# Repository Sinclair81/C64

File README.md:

# C64 #

## TinyAdapter (for Tiny-EPROMer from FaszinationC64.de) ##

<!-- markdownlint-disable MD033 -->

<!-- markdownlint-enable MD033 -->

### Adapterplatine für den Tiny-EPROMer ###

"Mit der kleinen, einfach nachzubauenden Zusatzplatine können Sie die Leistungsfähigkeit des Tiny-EPROMers
erheblich verbessern. So lassen sich mit ihr zusätzlich zu den EPROM-Typen 2764, 27128 und 27256 die Typen
27512 und 2732A proplemlos brennen und die im C64 eingebauten ROMs 2364 lesen."
64'er 12/1988 Seite 61

### Adapter board for the Tiny-EPROMer ###

"With the small, easy-to-rebuild additional circuit board, you can use the performance of the Tiny-EPROMer
improve significantly. In addition to the EPROM types 2764, 27128 and 27256, the types
Burn 27512 and 2732A without any problems and read the 2364 ROMs built into the C64."
64'er 12/1988 page 61

## Kernel adjustments ##

HEX address | description      | C64 Original                          | EXOS v3  
------------|------------------|---------------------------------------|--------  
0355        | font color       | 0E                                    | 0F  
0CD9        | edge color       | 0E                                    | 00  
0CDA        | background color | 06                                    | 00  
0460 - 0470 | Text 17 Byte     | " BASIC BYTES FREE"                   | " BASIC BYTES FREE"  
0475 - 0497 | Text 35 Byte     | "    **** COMMODORE 64 BASIC V2 ****" | "    *** C64 IMPROVED BY EXOS V3 ***"
049A - 04AA | Text 17 Byte     | " 64K RAM SYSTEM  "                   | "  BY J.SCHEMMEL  "

## Color palette ##

HEX | Color
----| -----
00  | black
01  | white
02  | red
03  | cyan
04  | violet
05  | green
06  | blue
07  | yellow
08  | orange
09  | brown
0A  | lightred
0B  | darkgrey
0C  | midgrey
0D  | lightgreen
0E  | lightblue
0F  | lightgrey

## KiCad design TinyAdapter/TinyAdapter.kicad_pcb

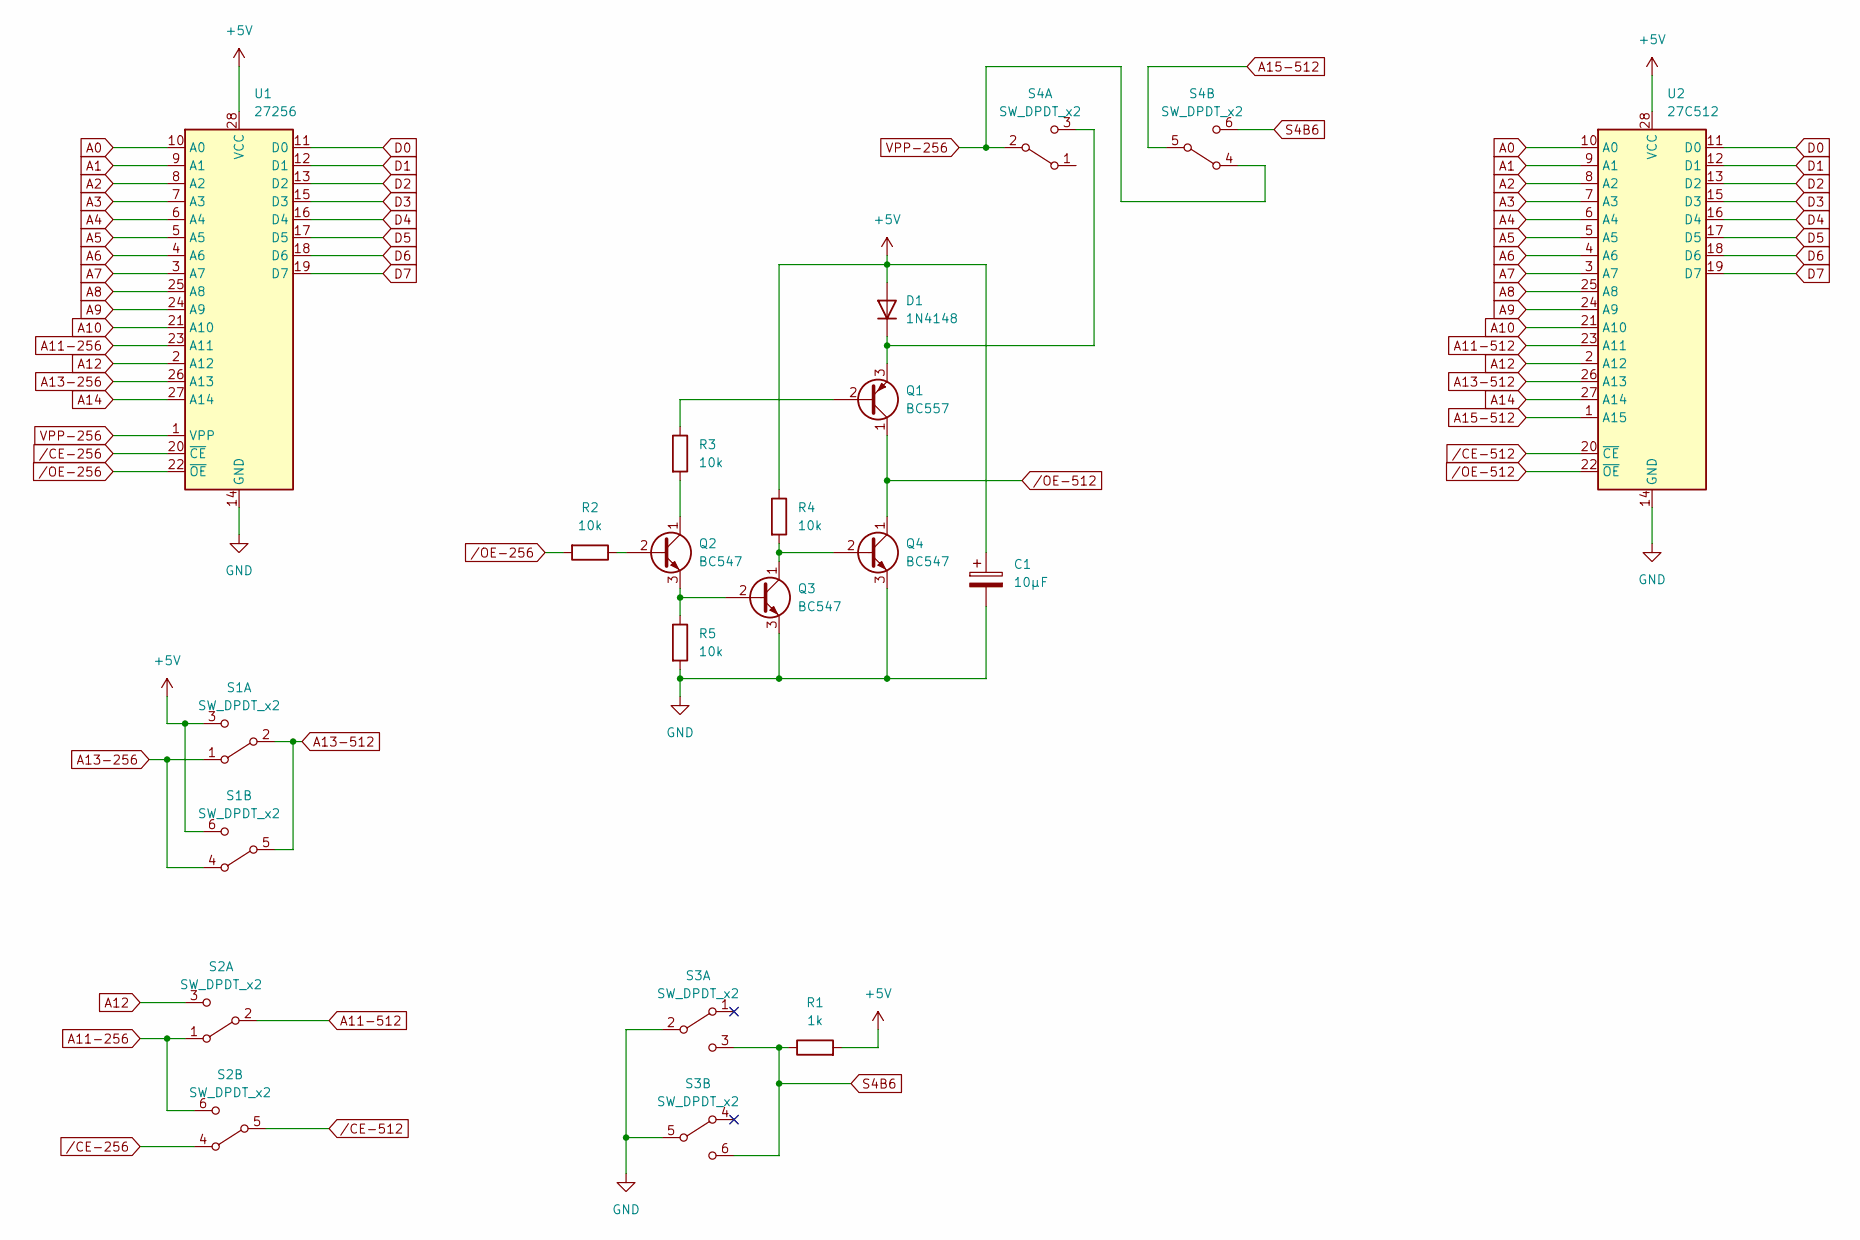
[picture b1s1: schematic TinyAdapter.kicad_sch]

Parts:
C1: 10µF; CP_Radial_D6.3mm_P2.50mm
D1: 1N4148; D_DO-35_SOD27_P7.62mm_Horizontal
Q1: BC557; TO-92_Inline
Q2, Q3, Q4: BC547; TO-92_Inline
R1: 1k; R_Axial_DIN0207_L6.3mm_D2.5mm_P10.16mm_Horizontal
R2, R3, R4, R5: 10k; R_Axial_DIN0207_L6.3mm_D2.5mm_P10.16mm_Horizontal
S1, S2, S3, S4: SW_DPDT_x2; SW_E-Switch_EG1271_DPDT_neu
U1: 27256; DIP-28_W15.24mm_Socket_LongPads
U2: 27C512; DIP_Socket-28_W11.9_W12.7_W15.24_W17.78_W18.5_3M_228-1277-0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

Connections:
+5V: C1.1, D1.2 (A), R1.2, R4.1, S1.3 (C), S1.6 (C), U1.28 (VCC), U2.28 (VCC)
A0: U1.10 (A0), U2.10 (A0)
A1: U1.9 (A1), U2.9 (A1)
A2: U1.8 (A2), U2.8 (A2)
A3: U1.7 (A3), U2.7 (A3)
A4: U1.6 (A4), U2.6 (A4)
A5: U1.5 (A5), U2.5 (A5)
A6: U1.4 (A6), U2.4 (A6)
A7: U1.3 (A7), U2.3 (A7)
A8: U1.25 (A8), U2.25 (A8)
A9: U1.24 (A9), U2.24 (A9)
A10: U1.21 (A10), U2.21 (A10)
A11-256: S2.1 (A), S2.6 (C), U1.23 (A11)
A11-512: S2.2 (B), U2.23 (A11)
A12: S2.3 (C), U1.2 (A12), U2.2 (A12)
A13-256: S1.1 (A), S1.4 (A), U1.26 (A13)
A13-512: S1.2 (B), S1.5 (B), U2.26 (A13)
A14: U1.27 (A14), U2.27 (A14)
A15-512: S4.5 (B), U2.1 (A15)
D0: U1.11 (D0), U2.11 (D0)
D1: U1.12 (D1), U2.12 (D1)
D2: U1.13 (D2), U2.13 (D2)
D3: U1.15 (D3), U2.15 (D3)
D4: U1.16 (D4), U2.16 (D4)
D5: U1.17 (D5), U2.17 (D5)
D6: U1.18 (D6), U2.18 (D6)
D7: U1.19 (D7), U2.19 (D7)
GND: C1.2, Q3.3 (E), Q4.3 (E), R5.2, S3.2 (B), S3.5 (B), U1.14 (GND), U2.14 (GND)
unnamed: D1.1 (K), Q1.3 (E), S4.3 (C)
unnamed: Q1.2 (B), R3.1
unnamed: Q2.1 (C), R3.2
unnamed: Q2.2 (B), R2.1
unnamed: Q2.3 (E), Q3.2 (B), R5.1
unnamed: Q3.1 (C), Q4.2 (B), R4.2
S4B6: R1.1, S3.3 (C), S3.6 (C), S4.6 (C)
VPP-256: S4.2 (B), S4.4 (A), U1.1 (VPP)
/CE-256: S2.4 (A), U1.20 (~CE)
/CE-512: S2.5 (B), U2.20 (~CE)
/OE-256: R2.2, U1.22 (~OE)
/OE-512: Q1.1 (C), Q4.1 (C), U2.22 (~OE)

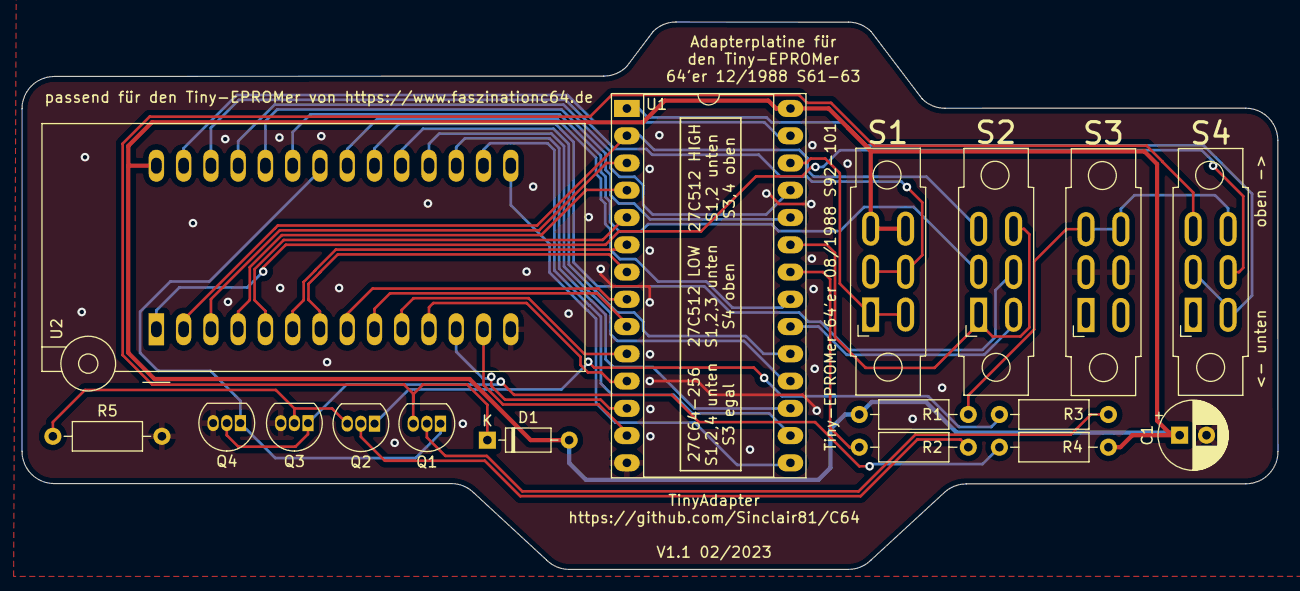
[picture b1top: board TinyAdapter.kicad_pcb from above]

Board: 2 copper layers, 117.0 x 51.0 mm, 17 parts (0 on the bottom side), 40 nets.

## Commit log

2023-02-09 add img's
2023-02-13 Add TinyAdapter
